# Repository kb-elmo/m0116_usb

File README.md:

# m0116_usb
[![CC BY-NC-SA 4.0][cc-by-nc-sa-shield]][cc-by-nc-sa]

## This project is completed and will not get updated anymore.

### QMK compatible drop-in replacement PCB for the Apple M0116
The PCB is built entirely with THT parts to keep a somewhat "vintage" look to it and it uses the fullsize 40-pin DIP package ATmega32A.
The controller is placed in the exact same location as the one on the original PCB meaning that it can be accessed through the plate cutout under the spacebar.

### Partslist
 |Count|Part|
 |-|-|
 |1|ATmega32A 40 pin DIP (32L works too)|
 |1|40 pin DIP socket (optional but highly recommended)|
 |1|2x3 pin header 2.54mm (for ISP flashing)|
 |1|JST PH 2mm 4pin connector + cable|
 |1|mini usb port|
 |1|500 mA polyfuse|
 |2|6mm momentary push buttons|
 |1|16 MHz quarz crystal|
 |1|4.7 uF electrolytic capacitor|
 |2|100 nF ceramic disk capacitor|
 |2|22 pF ceramic disk capacitor|
 |1|10 kΩ resistor|
 |2|68 Ω resistor|
 |1|1.5 kΩ resistor|
 |2|3.6 V zener diode (DO-35 BZX55C3V6)|
 |81|universal switching diode (DO-35 1N4148)|

#### Some pictures of the first finished PCB

This work is licensed under a
[Creative Commons Attribution-NonCommercial-ShareAlike 4.0 International License][cc-by-nc-sa].

[![CC BY-NC-SA 4.0][cc-by-nc-sa-image]][cc-by-nc-sa]

[cc-by-nc-sa]: http://creativecommons.org/licenses/by-nc-sa/4.0/
[cc-by-nc-sa-image]: https://licensebuttons.net/l/by-nc-sa/4.0/88x31.png
[cc-by-nc-sa-shield]: https://img.shields.io/badge/License-CC%20BY--NC--SA%204.0-lightgrey.svg

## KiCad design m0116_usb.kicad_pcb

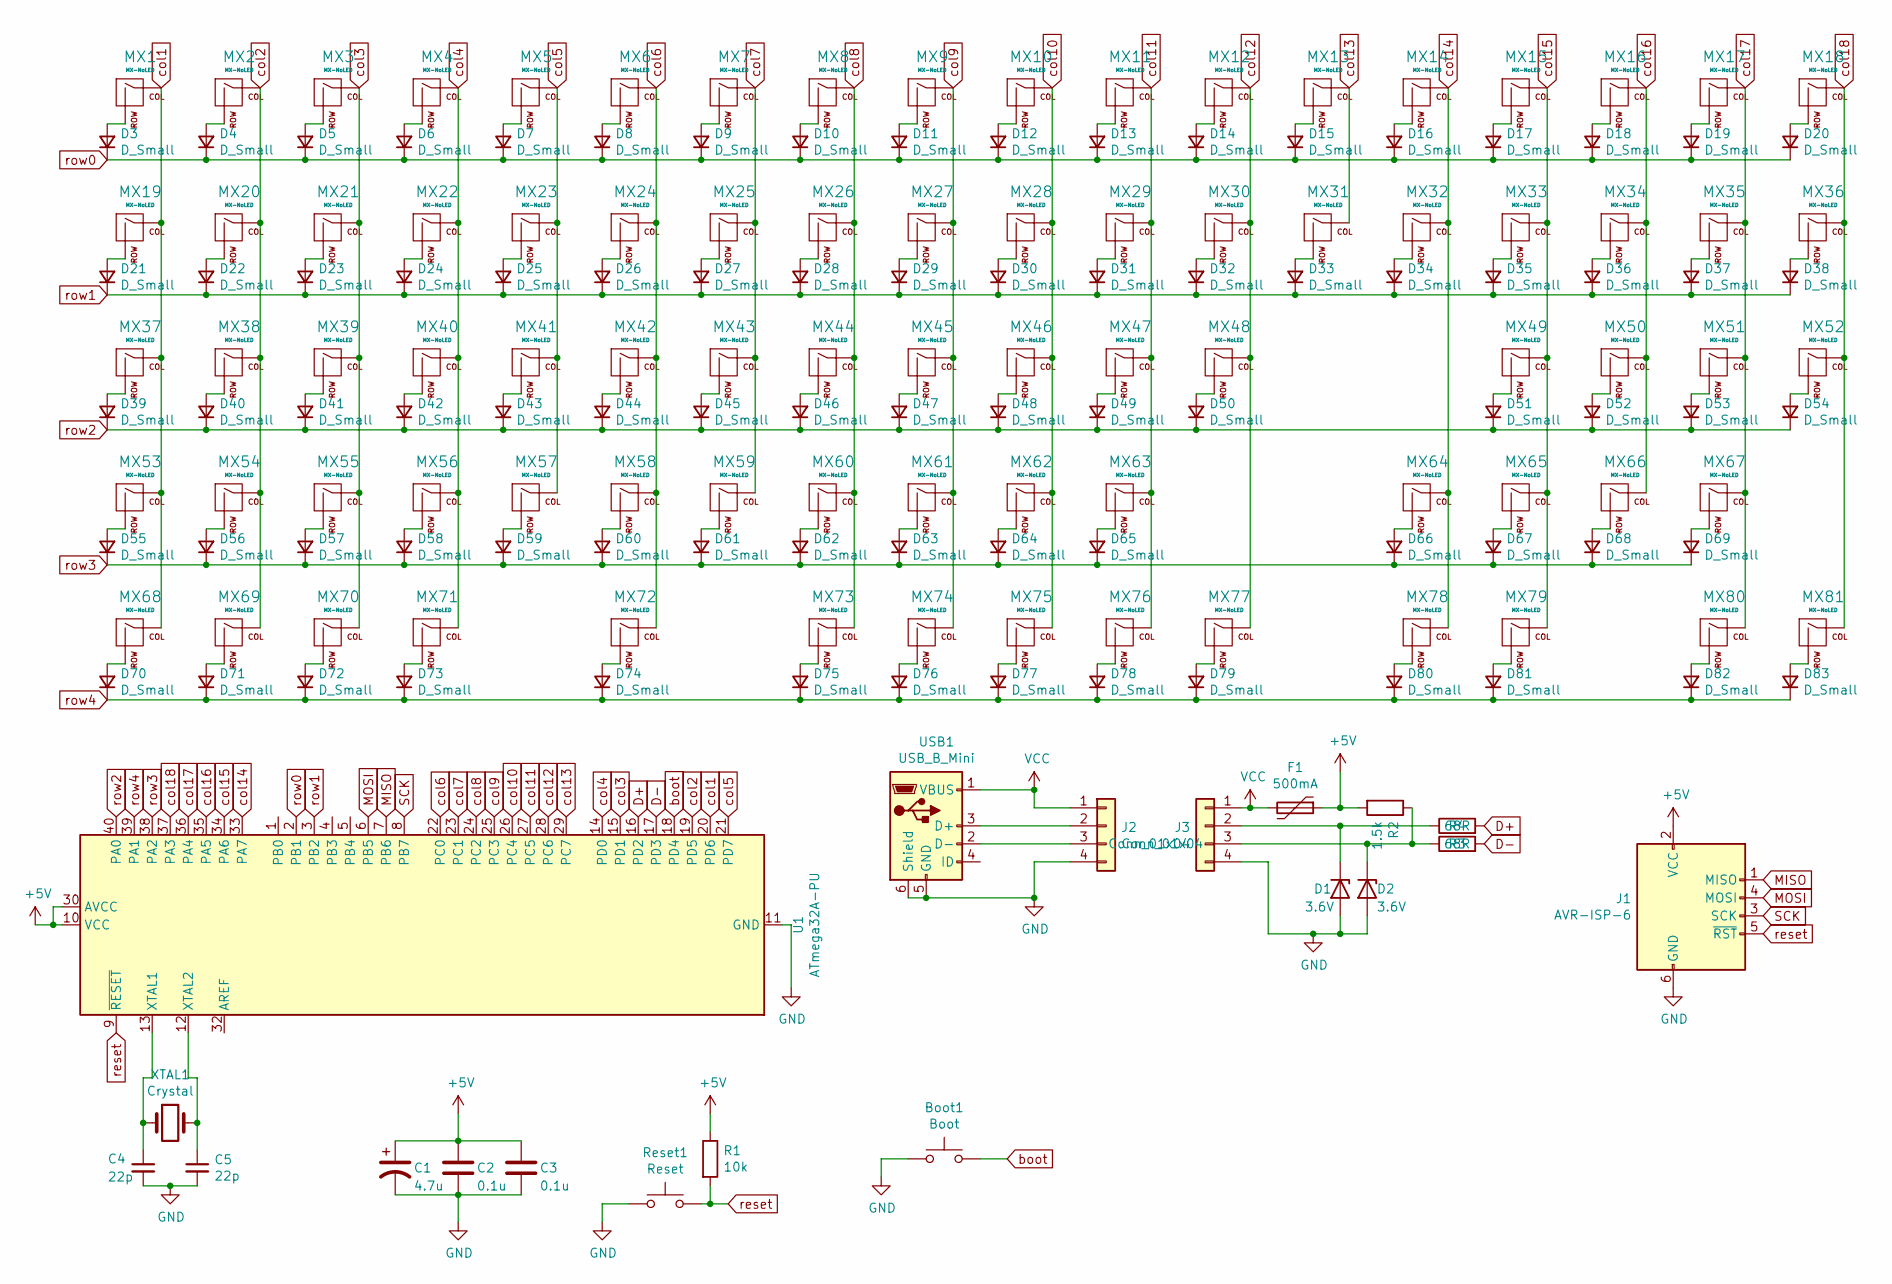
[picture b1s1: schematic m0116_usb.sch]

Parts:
Boot1: Boot; SW_PUSH_6mm
C1: 4.7u; CP_Radial_D5.0mm_P2.50mm
C2, C3: 0.1u; C_Disc_D3.0mm_W2.0mm_P2.50mm
C4, C5: 22p; C_Disc_D6.0mm_W2.5mm_P5.00mm
D1, D2: 3.6V; D_DO-35_SOD27_P7.62mm_Horizontal
D3, D4, D5, D6, D7, D8, D9, D10, D11, D12, D13, D14, D15, D16, D17, D18, D19, D20, D21, D22, D23, D24, D25, D26, D27, D28, D29, D30, D31, D32, D33, D34, D35, D36, D37, D38, D39, D40, D41, D42, D43, D44, D45, D46, D47, D48, D49, D50, D51, D52, D53, D54, D55, D56, D57, D58, D59, D60, D61, D62, D63, D64, D65, D66, D67, D68, D69, D70, D71, D72, D73, D74, D75, D76, D77, D78, D79, D80, D81, D82, D83: D_Small; D_DO-35_SOD27_P7.62mm_Horizontal
F1: 500mA; Fuse_Littelfuse_395Series
J1: AVR-ISP-6; PinHeader_2x03_P2.54mm_Horizontal
J2: Conn_01x04; PinHeader_1x04_P2.00mm_Vertical
J3: Conn_01x04; JST_PH_S4B-PH-K_1x04_P2.00mm_Horizontal
MX1, MX2, MX3, MX4, MX5, MX6, MX7, MX8, MX9, MX10, MX11, MX12, MX13, MX14, MX15, MX16, MX17, MX18, MX19, MX20, MX21, MX22, MX23, MX24, MX25, MX26, MX27, MX28, MX29, MX30, MX31, MX32, MX33, MX34, MX35, MX36, MX37, MX38, MX39, MX40, MX41, MX42, MX43, MX44, MX45, MX46, MX47, MX48, MX49, MX50, MX51, MX52, MX53, MX54, MX55, MX56, MX57, MX58, MX59, MX60, MX61, MX62, MX63, MX64, MX65, MX66, MX67, MX68, MX69, MX70, MX71, MX72, MX73, MX74, MX75, MX76, MX77, MX78, MX79, MX80, MX81: MX-NoLED; ALPS-1U
R1: 10k; R_Axial_DIN0207_L6.3mm_D2.5mm_P10.16mm_Horizontal
R2: 1.5k; R_Axial_DIN0207_L6.3mm_D2.5mm_P10.16mm_Horizontal
R3, R4: 68R; R_Axial_DIN0207_L6.3mm_D2.5mm_P10.16mm_Horizontal
Reset1: Reset; SW_PUSH_6mm
U1: ATmega32A-PU; DIP-40_W15.24mm_Socket
USB1: USB_B_Mini; Molex-0548190519
XTAL1: Crystal; Crystal_HC49-4H_Vertical

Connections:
+5V: C1.1, C2.1, C3.1, F1.1, J1.2 (VCC), R1.1, R2.2, U1.10 (VCC), U1.30 (AVCC)
D+: R3.2, U1.16 (PD2)
D-: R4.2, U1.17 (PD3)
GND: Boot1.1, C1.2, C2.2, C3.2, C4.2, C5.2, D1.2 (A), D2.2 (A), J1.6 (GND), J2.4, J3.4, Reset1.1, U1.11 (GND), U1.31 (GND), USB1.5 (GND), USB1.6 (Shield); also elsewhere on the board
MISO: J1.1 (MISO), U1.7 (PB6)
MOSI: J1.4 (MOSI), U1.6 (PB5)
unnamed: C4.1, U1.13 (XTAL1), XTAL1.1
unnamed: C5.1, U1.12 (XTAL2), XTAL1.2
unnamed: D1.1 (K), J3.2, R3.1
unnamed: D2.1 (K), J3.3, R2.1, R4.1
unnamed: D3.2 (A), MX1.2 (ROW)
unnamed: D4.2 (A), MX2.2 (ROW)
unnamed: D5.2 (A), MX3.2 (ROW)
unnamed: D6.2 (A), MX4.2 (ROW)
unnamed: D7.2 (A), MX5.2 (ROW)
unnamed: D8.2 (A), MX6.2 (ROW)
unnamed: D9.2 (A), MX7.2 (ROW)
unnamed: D10.2 (A), MX8.2 (ROW)
unnamed: D11.2 (A), MX9.2 (ROW)
unnamed: D12.2 (A), MX10.2 (ROW)
unnamed: D13.2 (A), MX11.2 (ROW)
unnamed: D14.2 (A), MX12.2 (ROW)
unnamed: D15.2 (A), MX13.2 (ROW)
unnamed: D16.2 (A), MX14.2 (ROW)
unnamed: D17.2 (A), MX15.2 (ROW)
unnamed: D18.2 (A), MX16.2 (ROW)
unnamed: D19.2 (A), MX17.2 (ROW)
unnamed: D20.2 (A), MX18.2 (ROW)
unnamed: D21.2 (A), MX19.2 (ROW)
unnamed: D22.2 (A), MX20.2 (ROW)
unnamed: D23.2 (A), MX21.2 (ROW)
unnamed: D24.2 (A), MX22.2 (ROW)
unnamed: D25.2 (A), MX23.2 (ROW)
unnamed: D26.2 (A), MX24.2 (ROW)
unnamed: D27.2 (A), MX25.2 (ROW)
unnamed: D28.2 (A), MX26.2 (ROW)
unnamed: D29.2 (A), MX27.2 (ROW)
unnamed: D30.2 (A), MX28.2 (ROW)
unnamed: D31.2 (A), MX29.2 (ROW)
unnamed: D32.2 (A), MX30.2 (ROW)
unnamed: D33.2 (A), MX31.2 (ROW)
unnamed: D34.2 (A), MX32.2 (ROW)
unnamed: D35.2 (A), MX33.2 (ROW)
unnamed: D36.2 (A), MX34.2 (ROW)
unnamed: D37.2 (A), MX35.2 (ROW)
unnamed: D38.2 (A), MX36.2 (ROW)
unnamed: D39.2 (A), MX37.2 (ROW)
unnamed: D40.2 (A), MX38.2 (ROW)
unnamed: D41.2 (A), MX39.2 (ROW)
unnamed: D42.2 (A), MX40.2 (ROW)
unnamed: D43.2 (A), MX41.2 (ROW)
unnamed: D44.2 (A), MX42.2 (ROW)
unnamed: D45.2 (A), MX43.2 (ROW)
unnamed: D46.2 (A), MX44.2 (ROW)
unnamed: D47.2 (A), MX45.2 (ROW)
unnamed: D48.2 (A), MX46.2 (ROW)
unnamed: D49.2 (A), MX47.2 (ROW)
unnamed: D50.2 (A), MX48.2 (ROW)
unnamed: D51.2 (A), MX49.2 (ROW)
unnamed: D52.2 (A), MX50.2 (ROW)
unnamed: D53.2 (A), MX51.2 (ROW)
unnamed: D54.2 (A), MX52.2 (ROW)
unnamed: D55.2 (A), MX53.2 (ROW)
unnamed: D56.2 (A), MX54.2 (ROW)
unnamed: D57.2 (A), MX55.2 (ROW)
unnamed: D58.2 (A), MX56.2 (ROW)
unnamed: D59.2 (A), MX57.2 (ROW)
unnamed: D60.2 (A), MX58.2 (ROW)
unnamed: D61.2 (A), MX59.2 (ROW)
unnamed: D62.2 (A), MX60.2 (ROW)
unnamed: D63.2 (A), MX61.2 (ROW)
unnamed: D64.2 (A), MX62.2 (ROW)
unnamed: D65.2 (A), MX63.2 (ROW)
unnamed: D66.2 (A), MX64.2 (ROW)
unnamed: D67.2 (A), MX65.2 (ROW)
unnamed: D68.2 (A), MX66.2 (ROW)
unnamed: D69.2 (A), MX67.2 (ROW)
unnamed: D70.2 (A), MX68.2 (ROW)
unnamed: D71.2 (A), MX69.2 (ROW)
unnamed: D72.2 (A), MX70.2 (ROW)
unnamed: D73.2 (A), MX71.2 (ROW)
unnamed: D74.2 (A), MX72.2 (ROW)
unnamed: D75.2 (A), MX73.2 (ROW)
unnamed: D76.2 (A), MX74.2 (ROW)
unnamed: D77.2 (A), MX75.2 (ROW)
unnamed: D78.2 (A), MX76.2 (ROW)
unnamed: D79.2 (A), MX77.2 (ROW)
unnamed: D80.2 (A), MX78.2 (ROW)
unnamed: D81.2 (A), MX79.2 (ROW)
unnamed: D82.2 (A), MX80.2 (ROW)
unnamed: D83.2 (A), MX81.2 (ROW)
unnamed: J2.2, USB1.3 (D+)
unnamed: J2.3, USB1.2 (D-)
SCK: J1.3 (SCK), U1.8 (PB7)
VCC: F1.2, J2.1, J3.1, USB1.1 (VBUS)
boot: Boot1.2, U1.18 (PD4); also elsewhere on the board
col1: MX1.1 (COL), MX19.1 (COL), MX37.1 (COL), MX53.1 (COL), MX68.1 (COL), U1.20 (PD6)
col2: MX2.1 (COL), MX20.1 (COL), MX38.1 (COL), MX54.1 (COL), MX69.1 (COL), U1.19 (PD5)
col3: MX3.1 (COL), MX21.1 (COL), MX39.1 (COL), MX55.1 (COL), MX70.1 (COL), U1.15 (PD1)
col4: MX4.1 (COL), MX22.1 (COL), MX40.1 (COL), MX56.1 (COL), MX71.1 (COL), U1.14 (PD0)
col5: MX5.1 (COL), MX23.1 (COL), MX41.1 (COL), MX57.1 (COL), U1.21 (PD7)
col6: MX6.1 (COL), MX24.1 (COL), MX42.1 (COL), MX58.1 (COL), MX72.1 (COL), U1.22 (PC0)
col7: MX7.1 (COL), MX25.1 (COL), MX43.1 (COL), MX59.1 (COL), U1.23 (PC1)
col8: MX8.1 (COL), MX26.1 (COL), MX44.1 (COL), MX60.1 (COL), MX73.1 (COL), U1.24 (PC2)
col9: MX9.1 (COL), MX27.1 (COL), MX45.1 (COL), MX61.1 (COL), MX74.1 (COL), U1.25 (PC3)
col10: MX10.1 (COL), MX28.1 (COL), MX46.1 (COL), MX62.1 (COL), MX75.1 (COL), U1.26 (PC4)
col11: MX11.1 (COL), MX29.1 (COL), MX47.1 (COL), MX63.1 (COL), MX76.1 (COL), U1.27 (PC5)
col12: MX12.1 (COL), MX30.1 (COL), MX48.1 (COL), MX77.1 (COL), U1.28 (PC6)
col13: MX13.1 (COL), MX31.1 (COL), U1.29 (PC7)
col14: MX14.1 (COL), MX32.1 (COL), MX64.1 (COL), MX78.1 (COL), U1.33 (PA7)
col15: MX15.1 (COL), MX33.1 (COL), MX49.1 (COL), MX65.1 (COL), MX79.1 (COL), U1.34 (PA6)
col16: MX16.1 (COL), MX34.1 (COL), MX50.1 (COL), MX66.1 (COL), U1.35 (PA5)
col17: MX17.1 (COL), MX35.1 (COL), MX51.1 (COL), MX67.1 (COL), MX80.1 (COL), U1.36 (PA4)
col18: MX18.1 (COL), MX36.1 (COL), MX52.1 (COL), MX81.1 (COL), U1.37 (PA3)
reset: J1.5 (~RST), R1.2, Reset1.2, U1.9 (~RESET); also elsewhere on the board
row0: D3.1 (K), D4.1 (K), D5.1 (K), D6.1 (K), D7.1 (K), D8.1 (K), D9.1 (K), D10.1 (K), D11.1 (K), D12.1 (K), D13.1 (K), D14.1 (K), D15.1 (K), D16.1 (K), D17.1 (K), D18.1 (K), D19.1 (K), D20.1 (K), U1.2 (PB1)
row1: D21.1 (K), D22.1 (K), D23.1 (K), D24.1 (K), D25.1 (K), D26.1 (K), D27.1 (K), D28.1 (K), D29.1 (K), D30.1 (K), D31.1 (K), D32.1 (K), D33.1 (K), D34.1 (K), D35.1 (K), D36.1 (K), D37.1 (K), D38.1 (K), U1.3 (PB2)
row2: D39.1 (K), D40.1 (K), D41.1 (K), D42.1 (K), D43.1 (K), D44.1 (K), D45.1 (K), D46.1 (K), D47.1 (K), D48.1 (K), D49.1 (K), D50.1 (K), D51.1 (K), D52.1 (K), D53.1 (K), D54.1 (K), U1.40 (PA0)
row3: D55.1 (K), D56.1 (K), D57.1 (K), D58.1 (K), D59.1 (K), D60.1 (K), D61.1 (K), D62.1 (K), D63.1 (K), D64.1 (K), D65.1 (K), D66.1 (K), D67.1 (K), D68.1 (K), D69.1 (K), U1.38 (PA2)
row4: D70.1 (K), D71.1 (K), D72.1 (K), D73.1 (K), D74.1 (K), D75.1 (K), D76.1 (K), D77.1 (K), D78.1 (K), D79.1 (K), D80.1 (K), D81.1 (K), D82.1 (K), D83.1 (K), U1.39 (PA1)

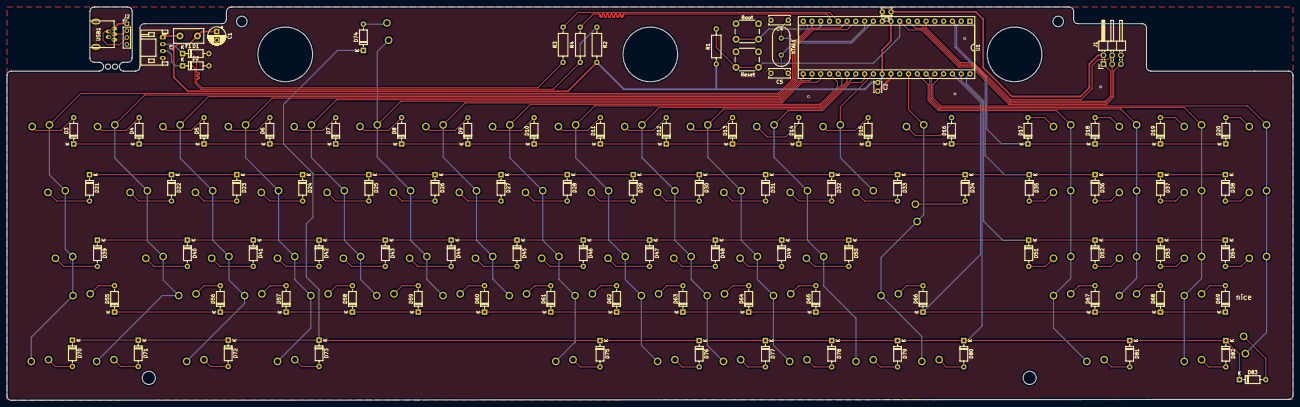
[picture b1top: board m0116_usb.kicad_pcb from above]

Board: 2 copper layers, 372.1 x 113.8 mm, 182 parts (0 on the bottom side), 120 nets.

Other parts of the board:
Boot: Boot; SW_PUSH_6mm
Reset: Reset; SW_PUSH_6mm

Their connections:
GND: Boot.1, Reset.1; also elsewhere on the board
boot: Boot.2; also elsewhere on the board
reset: Reset.2; also elsewhere on the board

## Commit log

2020-05-26 project start
2020-05-26 finished
2020-05-26 small fixes
2020-05-26 logos!
2020-05-26 gerbers
2020-05-26 make JLC happy
2020-05-26 fix wrong resistor connection
2020-06-03 rev1
2020-06-03 change design of daughterboard
2020-06-04 change JST connector size
2020-06-04 move the breakout pad to make JLC happy
2020-06-11 added firmware
2020-06-17 add guide
2020-06-20 update guide
2020-06-20 update guide (again)
2020-07-11 Update LICENSE
2020-07-13 fixed clearance issues with buttons
2020-08-05 readd submodule
